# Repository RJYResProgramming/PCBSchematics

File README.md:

# PCBSchematics
Schematics and Board Layouts for PCBs

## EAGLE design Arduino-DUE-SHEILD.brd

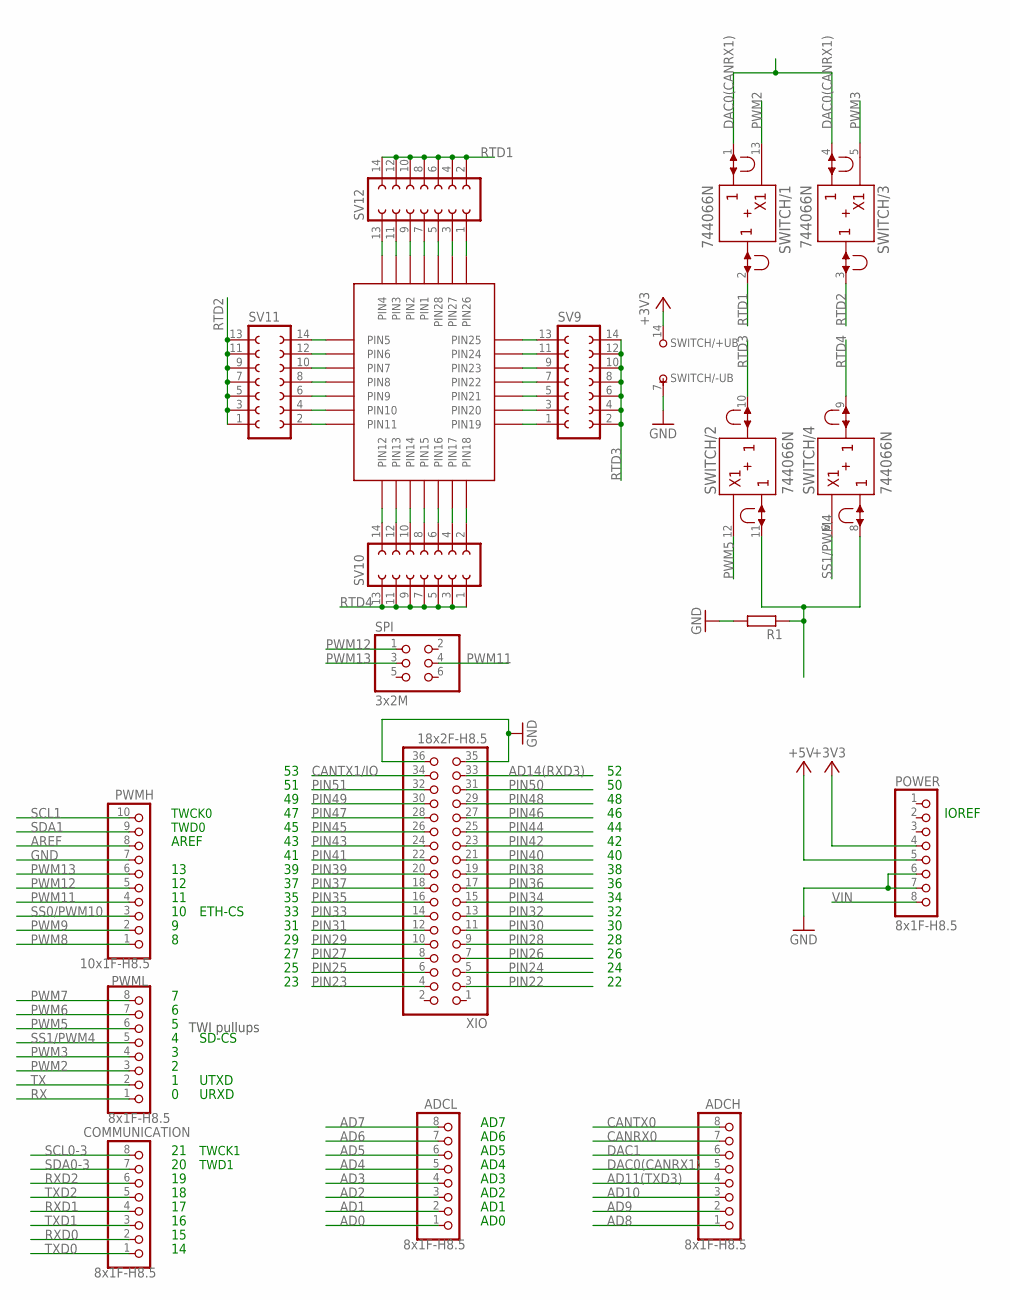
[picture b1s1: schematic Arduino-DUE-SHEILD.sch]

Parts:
ADCH: 8x1F-H8.5; 1X08
ADCL: 8x1F-H8.5; 1X08
COMMUNICATION: 8x1F-H8.5; 1X08
POWER: 8x1F-H8.5; 1X08
PWMH: 10x1F-H8.5; 1X10
PWML: 8x1F-H8.5; 1X08
R1: R-EU_0207/7; 0207/7
SPI: 3x2M; 2X03
SV9, SV10, SV11, SV12: FE07-2
SWITCH: 744066N; DIL14
U$1: S28
XIO: 18x2F-H8.5; 2X18

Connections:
+3V3: POWER.4, SWITCH.14 (+UB)
+5V: POWER.5
AD0: ADCL.1
AD1: ADCL.2
AD2: ADCL.3
AD3: ADCL.4
AD4: ADCL.5
AD5: ADCL.6, R1.1, SWITCH.8 (A), SWITCH.11 (A)
AD6: ADCL.7
AD7: ADCL.8
AD8: ADCH.1
AD9: ADCH.2
AD10: ADCH.3
AD11(TXD3): ADCH.4
AD14(RXD3): XIO.33
AREF: PWMH.8
CANRX0: ADCH.7
CANTX0: ADCH.8
CANTX1/IO: XIO.34
DAC0(CANRX1): ADCH.5, SWITCH.1 (A), SWITCH.4 (A)
DAC1: ADCH.6
GND: POWER.6, POWER.7, PWMH.7, R1.2, SWITCH.7 (-UB), XIO.35, XIO.36
unnamed: SV12.13, U$1.4 (PIN4)
unnamed: SV12.11, U$1.3 (PIN3)
unnamed: SV12.9, U$1.2 (PIN2)
unnamed: SV12.7, U$1.1 (PIN1)
unnamed: SV12.3, U$1.27 (PIN27)
unnamed: SV12.5, U$1.28 (PIN28)
unnamed: SV12.1, U$1.26 (PIN26)
unnamed: SV9.13, U$1.25 (PIN25)
unnamed: SV9.11, U$1.24 (PIN24)
unnamed: SV9.9, U$1.23 (PIN23)
unnamed: SV9.7, U$1.22 (PIN22)
unnamed: SV9.5, U$1.21 (PIN21)
unnamed: SV9.3, U$1.20 (PIN20)
unnamed: SV9.1, U$1.19 (PIN19)
unnamed: SV11.14, U$1.5 (PIN5)
unnamed: SV11.12, U$1.6 (PIN6)
unnamed: SV11.10, U$1.7 (PIN7)
unnamed: SV11.8, U$1.8 (PIN8)
unnamed: SV11.6, U$1.9 (PIN9)
unnamed: SV11.4, U$1.10 (PIN10)
unnamed: SV11.2, U$1.11 (PIN11)
unnamed: SV10.14, U$1.12 (PIN12)
unnamed: SV10.12, U$1.13 (PIN13)
unnamed: SV10.10, U$1.14 (PIN14)
unnamed: SV10.8, U$1.15 (PIN15)
unnamed: SV10.6, U$1.16 (PIN16)
unnamed: SV10.4, U$1.17 (PIN17)
unnamed: SV10.2, U$1.18 (PIN18)
PIN22: XIO.3
PIN23: XIO.4
PIN24: XIO.5
PIN25: XIO.6
PIN26: XIO.7
PIN27: XIO.8
PIN28: XIO.9
PIN29: XIO.10
PIN30: XIO.11
PIN31: XIO.12
PIN32: XIO.13
PIN33: XIO.14
PIN34: XIO.15
PIN35: XIO.16
PIN36: XIO.17
PIN37: XIO.18
PIN38: XIO.19
PIN39: XIO.20
PIN40: XIO.21
PIN41: XIO.22
PIN42: XIO.23
PIN43: XIO.24
PIN44: XIO.25
PIN45: XIO.26
PIN46: XIO.27
PIN47: XIO.28
PIN48: XIO.29
PIN49: XIO.30
PIN50: XIO.31
PIN51: XIO.32
PWM2: PWML.3, SWITCH.13 (C)
PWM3: PWML.4, SWITCH.5 (C)
PWM5: PWML.6, SWITCH.12 (C)
PWM6: PWML.7
PWM7: PWML.8
PWM8: PWMH.1
PWM9: PWMH.2
PWM11: PWMH.4, SPI.4
PWM12: PWMH.5, SPI.1
PWM13: PWMH.6, SPI.3
RTD1: SV12.2, SV12.4, SV12.6, SV12.8, SV12.10, SV12.12, SV12.14, SWITCH.2 (B)
RTD2: SV11.1, SV11.3, SV11.5, SV11.7, SV11.9, SV11.11, SV11.13, SWITCH.3 (B)
RTD3: SV9.2, SV9.4, SV9.6, SV9.8, SV9.10, SV9.12, SV9.14, SWITCH.10 (B)
RTD4: SV10.1, SV10.3, SV10.5, SV10.7, SV10.9, SV10.11, SV10.13, SWITCH.9 (B)
RX: PWML.1
RXD0: COMMUNICATION.2
RXD1: COMMUNICATION.4
RXD2: COMMUNICATION.6
SCL0-3: COMMUNICATION.8
SCL1: PWMH.10
SDA0-3: COMMUNICATION.7
SDA1: PWMH.9
SS0/PWM10: PWMH.3
SS1/PWM4: PWML.5, SWITCH.6 (C)
TX: PWML.2
TXD0: COMMUNICATION.1
TXD1: COMMUNICATION.3
TXD2: COMMUNICATION.5
VIN: POWER.8

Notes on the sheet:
TWI pullups
TWCK1
TWD1
IOREF
TWCK0
TWD0
AD1
AD2
AD3
AD4
AD5
AD6
AD0
AREF
AD7
SD-CS
UTXD
URXD
ETH-CS

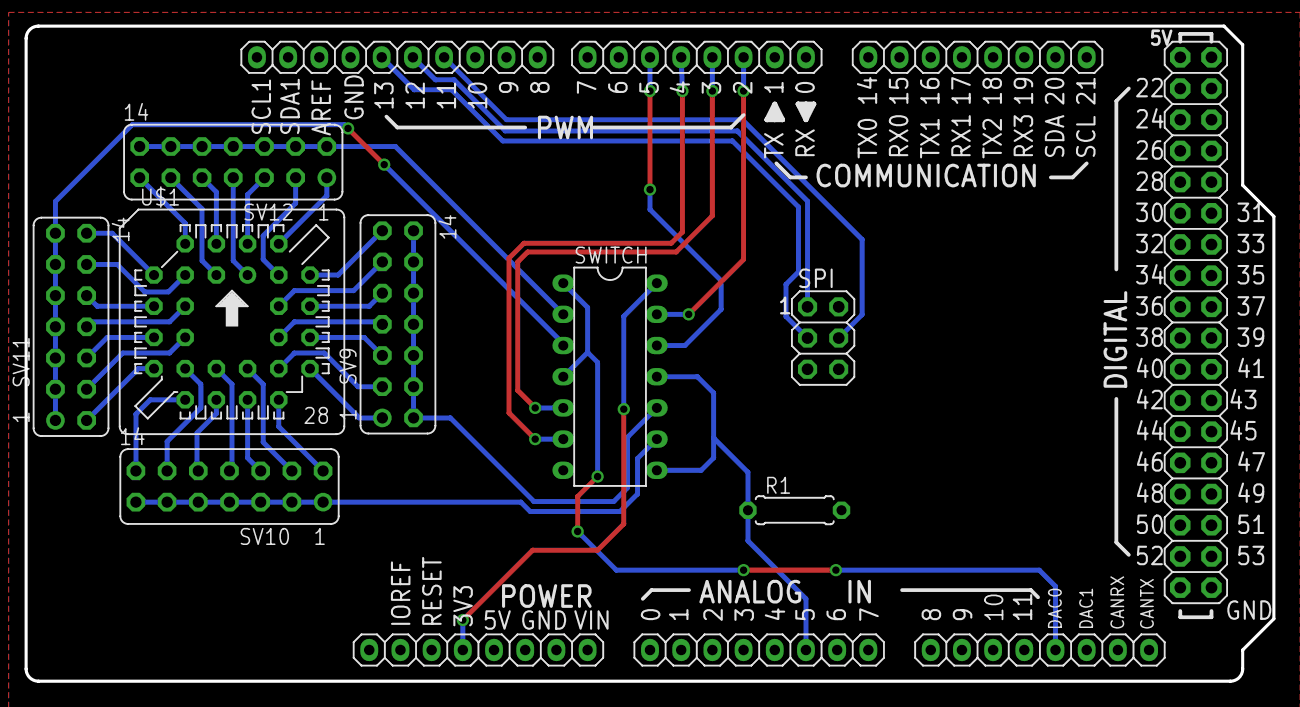
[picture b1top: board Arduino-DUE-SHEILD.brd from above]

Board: 2 copper layers, 101.6 x 53.3 mm, 15 parts (0 on the bottom side), 43 nets.
